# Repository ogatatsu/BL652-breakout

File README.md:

# BL652-breakout

LairdTechのnRF52832モジュールBL652のブレークアウト基板

Adafruit [Feather nRF52](https://www.adafruit.com/product/3406)の[ブートローダー](https://github.com/adafruit/Adafruit_nRF52_Arduino)を書き込むことを意識して設計してあり、書き込み後はArduino Pro Mini用のusbシリアル変換アダプタを挿せばArduinoで開発できます

## 部品表

| Name | Qty | Description | Manufacturer
----|----|----|----
| U1 | 1 | BL652-SA-01 | LairdTech |
| Y1 | 1 | Crystal, FC-135, 32.768kHz, 9pF | EPSON |
| C1,C4 | 2 | Capacitor, 0.1uF, 1608 ||
| C2,C3 | 2 | Capacitor, 12pF, 1608 ||
| R1 | 1 | Resistor, 1k Ohm, 1608 ||
| R2 | 1 | Resistor, 330 Ohm, 1608 ||
| R3 | 1 | Resistor, 10k Ohm, 1608 ||
| D1 | 1 | Diode, 1N4148W | Diodes Incorporated |
| LED1 | 1 | Led, Red, 1608 ||
| LED2 | 1 | Led, Yellow Green, 1608 ||

## License

https://creativecommons.org/licenses/by/4.0/

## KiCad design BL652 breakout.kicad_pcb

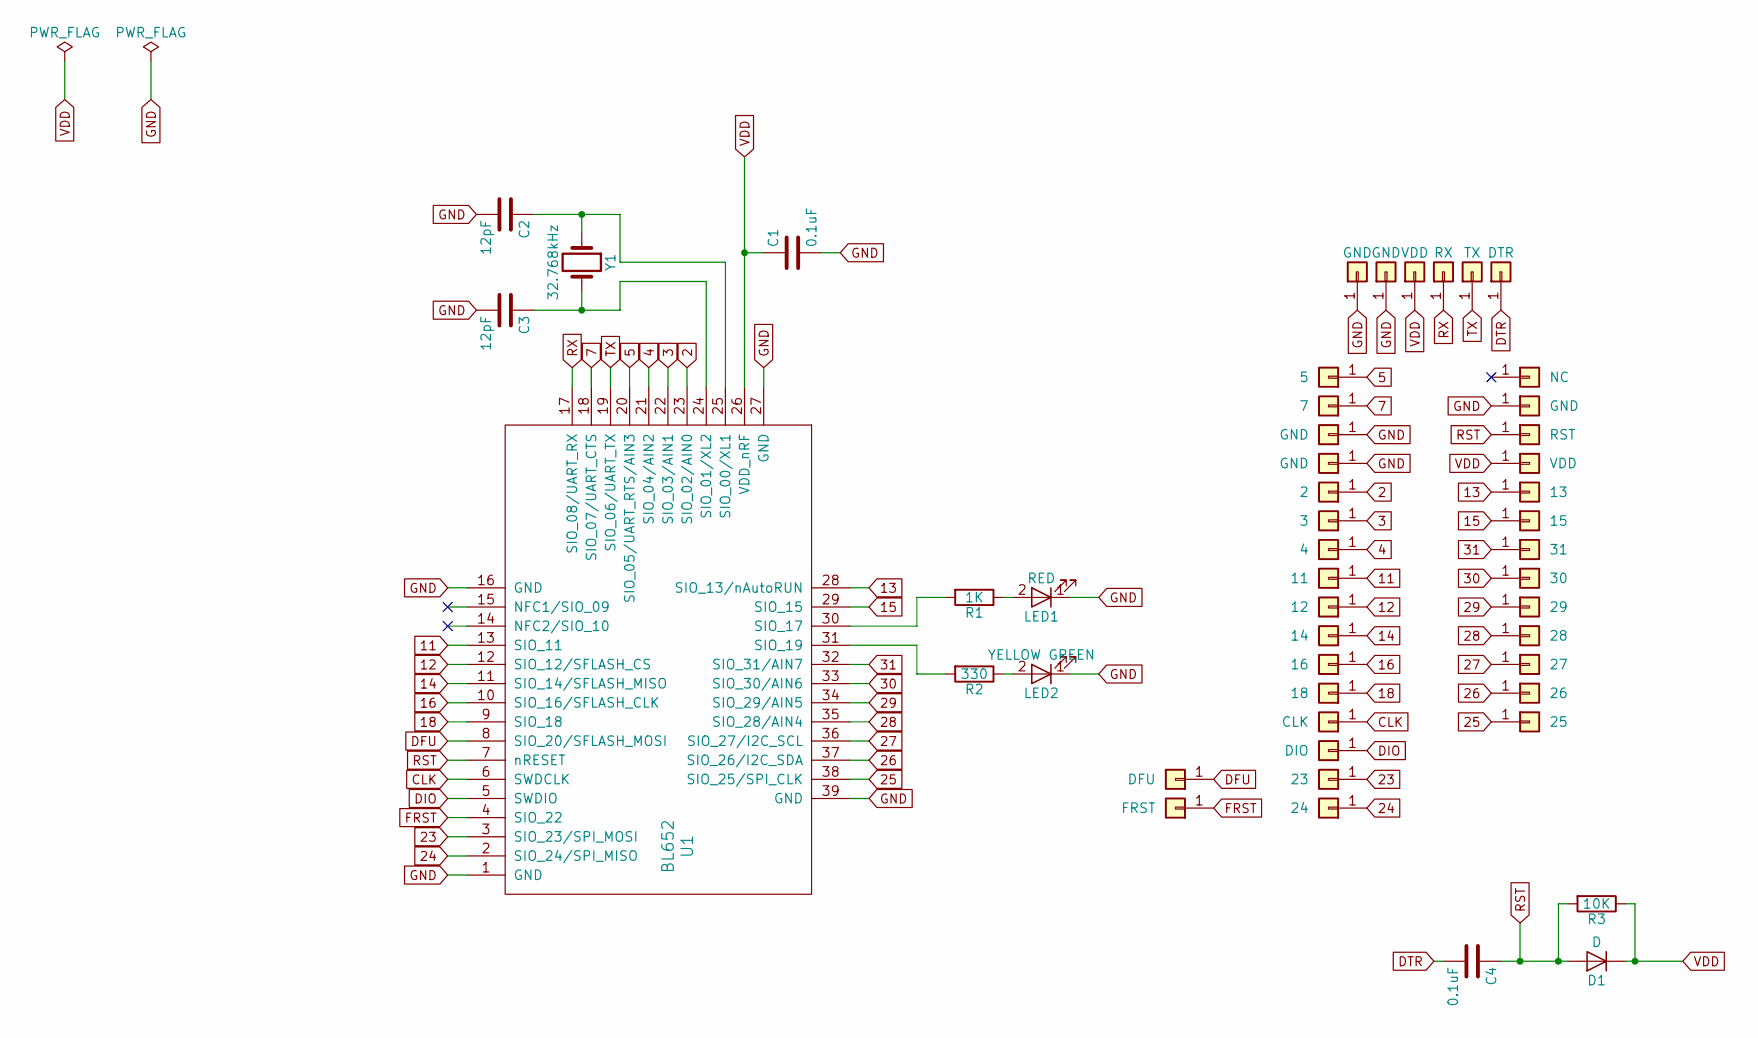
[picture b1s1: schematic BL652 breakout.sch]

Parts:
C1, C4: 0.1uF; 1608
C2, C3: 12pF; 1608
D1: D; Diode
LED1: RED; 1608
LED2: YELLOW GREEN; 1608
P2: 2; Wirepad
P3: 3; Wirepad
P4: 4; Wirepad
P5: 5; Wirepad
P7: 7; Wirepad
P11: 11; Wirepad
P12: 12; Wirepad
P13: 13; Wirepad
P14: 14; Wirepad
P15: 15; Wirepad
P16: 16; Wirepad
P18: 18; Wirepad
P23: 23; Wirepad
P24: 24; Wirepad
P25: 25; Wirepad
P26: 26; Wirepad
P27: 27; Wirepad
P28: 28; Wirepad
P29: 29; Wirepad
P30: 30; Wirepad
P31: 31; Wirepad
PCLK1: CLK; Wirepad
PDFU1: DFU; Circle
PDIO1: DIO; Wirepad
PDTR1: DTR; Wirepad
PFRST1: FRST; Circle
PGND1, PGND2, PGND3, PGND4, PGND5: GND; Wirepad
PNC2: NC; Wirepad
PRST1: RST; Wirepad
PRX1: RX; Wirepad
PTX1: TX; Wirepad
PVDD1, PVDD2: VDD; Wirepad
R1: 1K; 1608
R2: 330; 1608
R3: 10K; 1608
U1: BL652
Y1: 32.768kHz; FC-135

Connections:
2: P2.1, U1.23 (SIO_02/AIN0)
3: P3.1, U1.22 (SIO_03/AIN1)
4: P4.1, U1.21 (SIO_04/AIN2)
5: P5.1, U1.20 (SIO_05/UART_RTS/AIN3)
7: P7.1, U1.18 (SIO_07/UART_CTS)
11: P11.1, U1.13 (SIO_11)
12: P12.1, U1.12 (SIO_12/SFLASH_CS)
13: P13.1, U1.28 (SIO_13/nAutoRUN)
14: P14.1, U1.11 (SIO_14/SFLASH_MISO)
15: P15.1, U1.29 (SIO_15)
16: P16.1, U1.10 (SIO_16/SFLASH_CLK)
18: P18.1, U1.9 (SIO_18)
23: P23.1, U1.3 (SIO_23/SPI_MOSI)
24: P24.1, U1.2 (SIO_24/SPI_MISO)
25: P25.1, U1.38 (SIO_25/SPI_CLK)
26: P26.1, U1.37 (SIO_26/I2C_SDA)
27: P27.1, U1.36 (SIO_27/I2C_SCL)
28: P28.1, U1.35 (SIO_28/AIN4)
29: P29.1, U1.34 (SIO_29/AIN5)
30: P30.1, U1.33 (SIO_30/AIN6)
31: P31.1, U1.32 (SIO_31/AIN7)
CLK: PCLK1.1, U1.6 (SWDCLK)
DFU: PDFU1.1, U1.8 (SIO_20/SFLASH_MOSI)
DIO: PDIO1.1, U1.5 (SWDIO)
DTR: C4.2, PDTR1.1
FRST: PFRST1.1, U1.4 (SIO_22)
GND: C1.2, C2.2, C3.2, LED1.1 (K), LED2.1 (K), PGND1.1, PGND2.1, PGND3.1, PGND4.1, PGND5.1, U1.1 (GND), U1.16 (GND), U1.27 (GND), U1.39 (GND)
unnamed: C2.1, U1.25 (SIO_00/XL1), Y1.1
unnamed: C3.1, U1.24 (SIO_01/XL2), Y1.2
unnamed: LED1.2 (A), R1.1
unnamed: LED2.2 (A), R2.1
unnamed: R1.2, U1.30 (SIO_17)
unnamed: R2.2, U1.31 (SIO_19)
RST: C4.1, D1.2 (A), PRST1.1, R3.2, U1.7 (nRESET)
RX: PRX1.1, U1.17 (SIO_08/UART_RX)
TX: PTX1.1, U1.19 (SIO_06/UART_TX)
VDD: C1.1, D1.1 (K), PVDD1.1, PVDD2.1, R3.1, U1.26 (VDD_nRF)

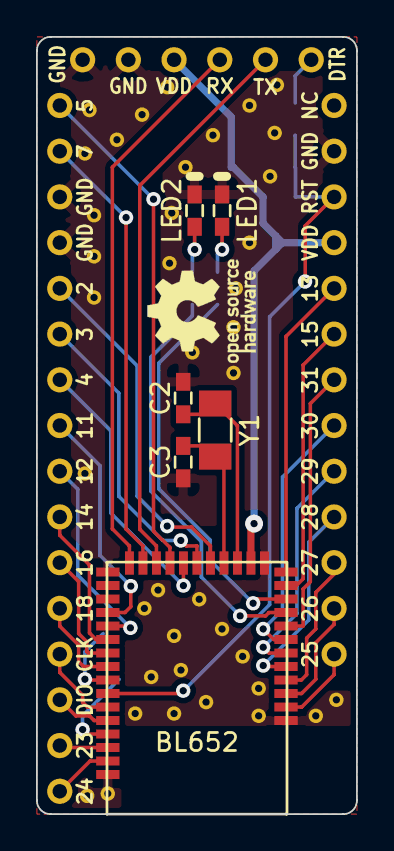
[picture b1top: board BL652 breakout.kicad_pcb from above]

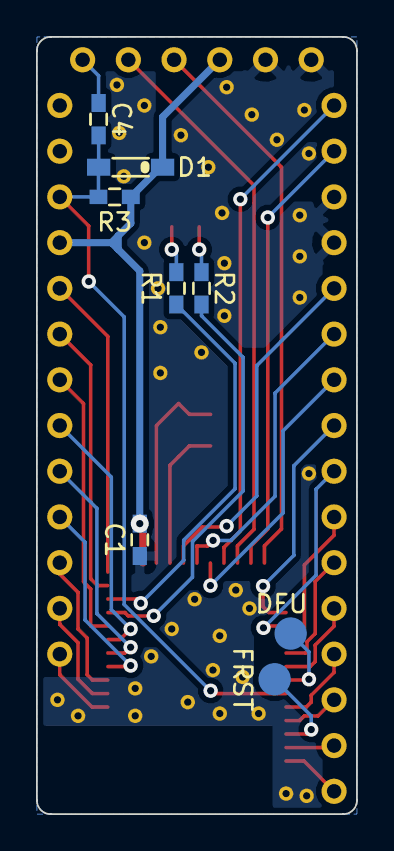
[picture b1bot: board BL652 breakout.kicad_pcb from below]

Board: 2 copper layers, 17.8 x 43.2 mm, 49 parts (8 on the bottom side), 37 nets.

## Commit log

2018-01-12 add images
